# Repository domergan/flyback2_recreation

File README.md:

# Recreation of a Resonant Flyback Driver

A recreation of the Easy-Flyback driver by Franzoli Electronics: a resonant driver for CRT TV flyback transformers that produces high-voltage arcs, which can be audio-modulated to play music.
This repository contains a redrawn schematic and PCB layout based on his schematic published publicly on his page (https://franzolielectronics.com/easy-flyback-i/).

> All credit for the original circuit design goes to Franzoli!

&nbsp;

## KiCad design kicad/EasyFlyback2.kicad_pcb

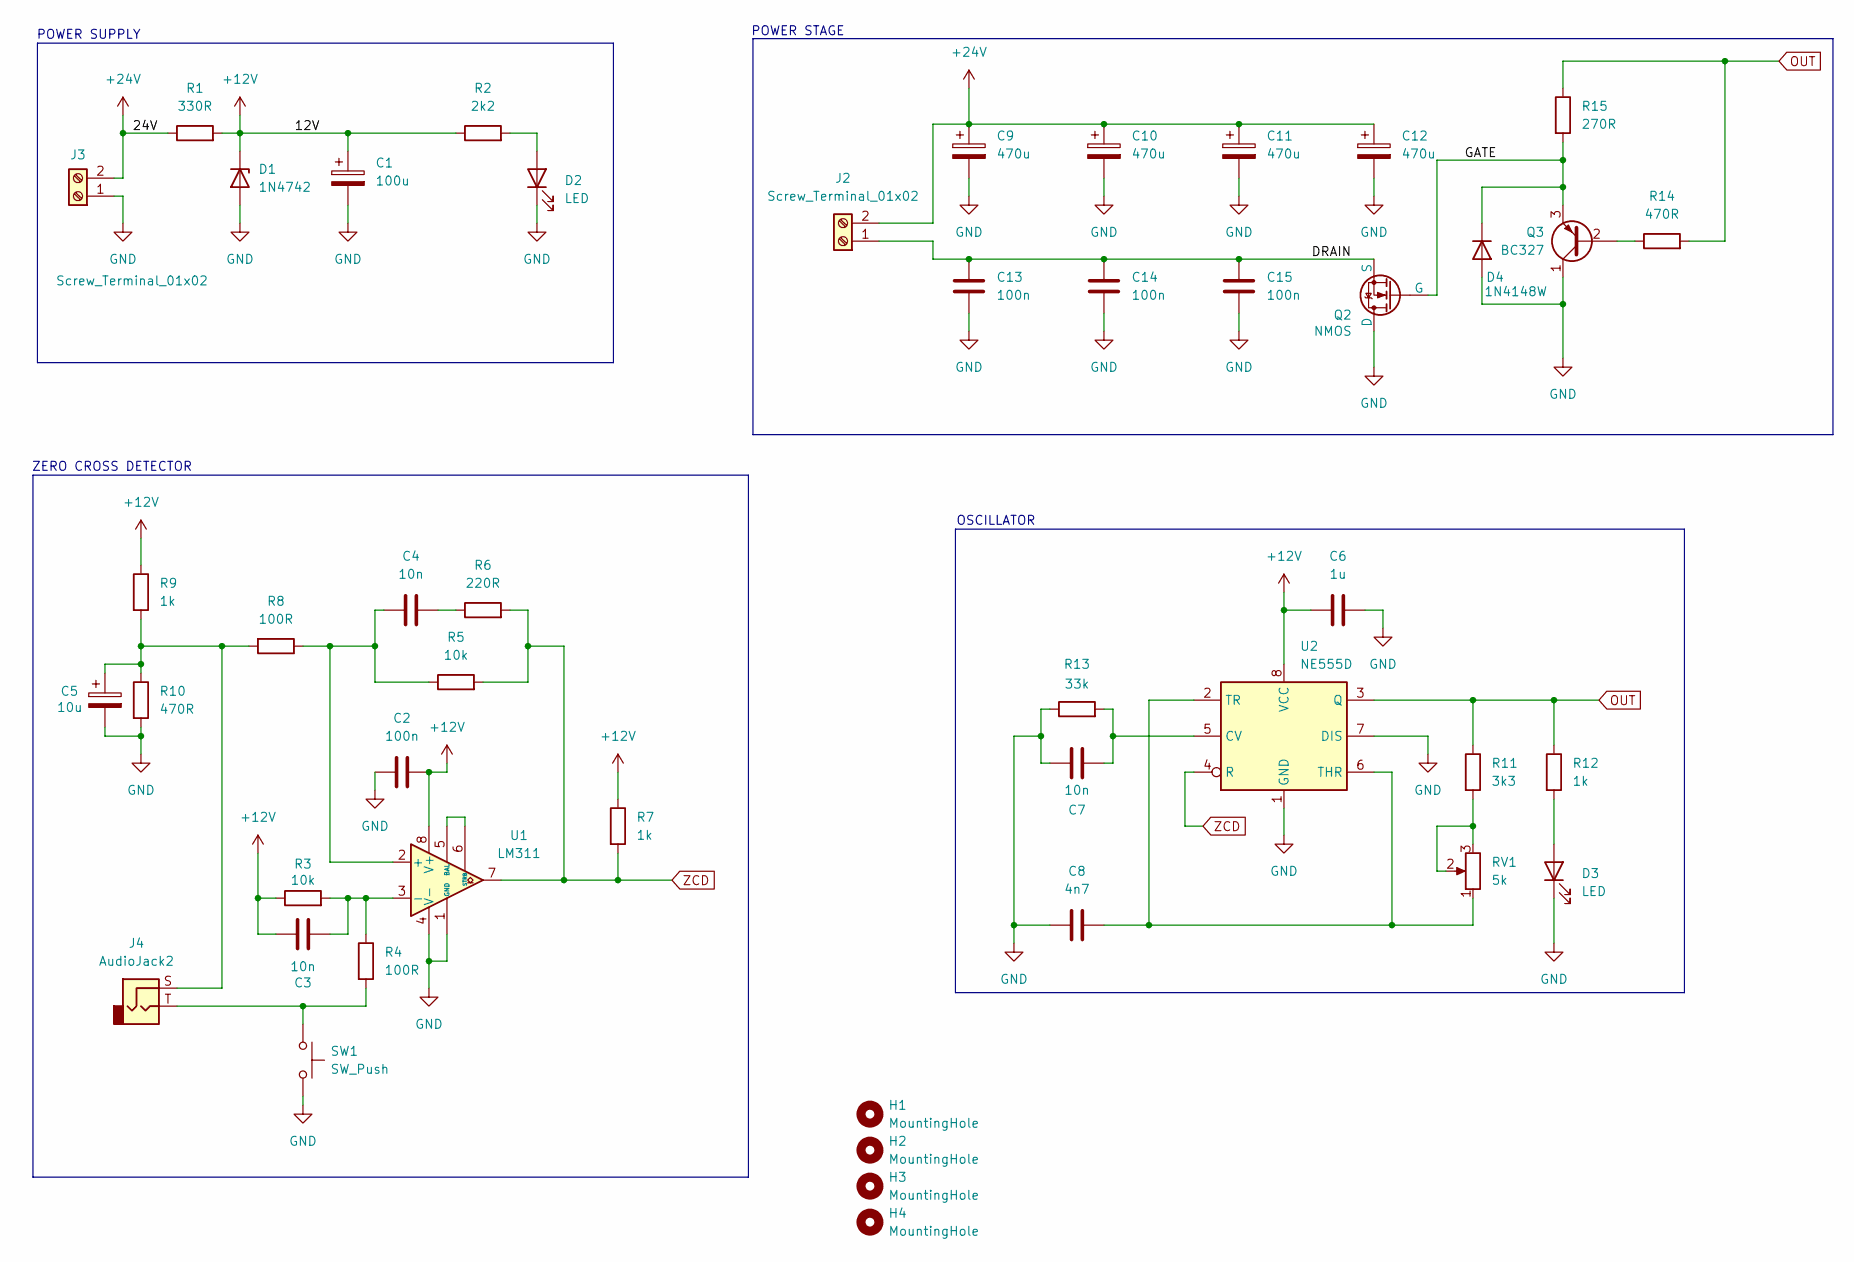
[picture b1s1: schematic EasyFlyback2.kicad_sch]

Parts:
C1: 100u; CP_Radial_D5.0mm_P2.00mm
C2: 100n; C_Rect_L7.0mm_W2.5mm_P5.00mm
C3, C4, C7: 10n; C_Rect_L7.0mm_W2.5mm_P5.00mm
C5: 10u; CP_Radial_D4.0mm_P1.50mm
C6: 1u; CP_Radial_D5.0mm_P2.00mm
C8: 4n7; C_Rect_L7.0mm_W2.5mm_P5.00mm
C9, C10, C11, C12: 470u; CP_Radial_D10.0mm_P5.00mm
C13, C14, C15: 100n; C_Rect_L18.0mm_W6.0mm_P15.00mm_FKS3_FKP3
D1: 1N4742; D_DO-41_SOD81_P7.62mm_Horizontal
D2, D3: LED; LED_D5.0mm
D4: 1N4148W; D_SOD-123
H1, H2, H3, H4: MountingHole; MountingHole_3.2mm_M3_ISO7380_Pad_TopOnly
J2, J3: Screw_Terminal_01x02; Altech_AK100_1x02_P5.00mm
J4: AudioJack2; Jack_3.5mm_CUI_SJ1-3525N_Horizontal
Q2: NMOS; TO-247-3_Horizontal_TabDown
Q3: BC327; TO-92_Inline
R1: 330R; R_Axial_DIN0516_L15.5mm_D5.0mm_P20.32mm_Horizontal
R2: 2k2; R_Axial_DIN0207_L6.3mm_D2.5mm_P10.16mm_Horizontal
R3, R5: 10k; R_Axial_DIN0207_L6.3mm_D2.5mm_P10.16mm_Horizontal
R4, R8: 100R; R_Axial_DIN0207_L6.3mm_D2.5mm_P10.16mm_Horizontal
R6: 220R; R_Axial_DIN0207_L6.3mm_D2.5mm_P10.16mm_Horizontal
R7, R9, R12: 1k; R_Axial_DIN0207_L6.3mm_D2.5mm_P10.16mm_Horizontal
R10, R14: 470R; R_Axial_DIN0207_L6.3mm_D2.5mm_P10.16mm_Horizontal
R11: 3k3; R_Axial_DIN0207_L6.3mm_D2.5mm_P10.16mm_Horizontal
R13: 33k; R_Axial_DIN0207_L6.3mm_D2.5mm_P10.16mm_Horizontal
R15: 270R; R_Axial_DIN0207_L6.3mm_D2.5mm_P10.16mm_Horizontal
RV1: 5k; Potentiometer_Bourns_3296W_Vertical
SW1: SW_Push; SW_PUSH_6mm
U1: LM311; DIP-8_W7.62mm_Socket
U2: NE555D; DIP-8_W7.62mm_Socket

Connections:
+12V: C1.1, C2.2, C3.1, C6.1, D1.1 (K), R1.2, R2.1, R3.1, R7.1, R9.1, U1.8 (V+), U2.8 (VCC)
+24V: C9.1, C10.1, C11.1, C12.1, J2.2, J3.2, R1.1
/DRAIN: C13.1, C14.1, C15.1, J2.1, Q2.3 (S)
/GATE: D4.1 (K), Q2.2 (G), Q3.3 (E), R15.2
GND: C1.2, C2.1, C5.2, C6.2, C7.1, C8.1, C9.2, C10.2, C11.2, C12.2, C13.2, C14.2, C15.2, D1.2 (A), D2.1 (K), D3.1 (K), D4.2 (A), J3.1, Q2.1 (D), Q3.1 (C), R10.2, R13.1, SW1.2, U1.1 (GND), U1.4 (V-), U2.1 (GND), U2.7 (DIS)
unnamed: C4.2, R6.1
unnamed: C5.1, J4.S, R8.2, R9.2, R10.1
unnamed: D2.2 (A), R2.2
unnamed: D3.2 (A), R12.2
unnamed: J4.T, R4.2, SW1.1
unnamed: Q3.2 (B), R14.1
unnamed: R11.2, RV1.2, RV1.3
unnamed: C4.1, R5.1, R8.1, U1.2 (+)
unnamed: C3.2, R3.2, R4.1, U1.3 (-)
unnamed: U1.5 (BAL), U1.6 (STRB)
unnamed: C7.2, R13.2, U2.5 (CV)
unnamed: C8.2, RV1.1, U2.2 (TR), U2.6 (THR)
OUT: R11.1, R12.1, R14.2, R15.1, U2.3 (Q)
ZCD: R5.2, R6.2, R7.2, U1.7, U2.4 (R)

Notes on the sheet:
OSCILLATOR
POWER SUPPLY
ZERO CROSS DETECTOR
POWER STAGE

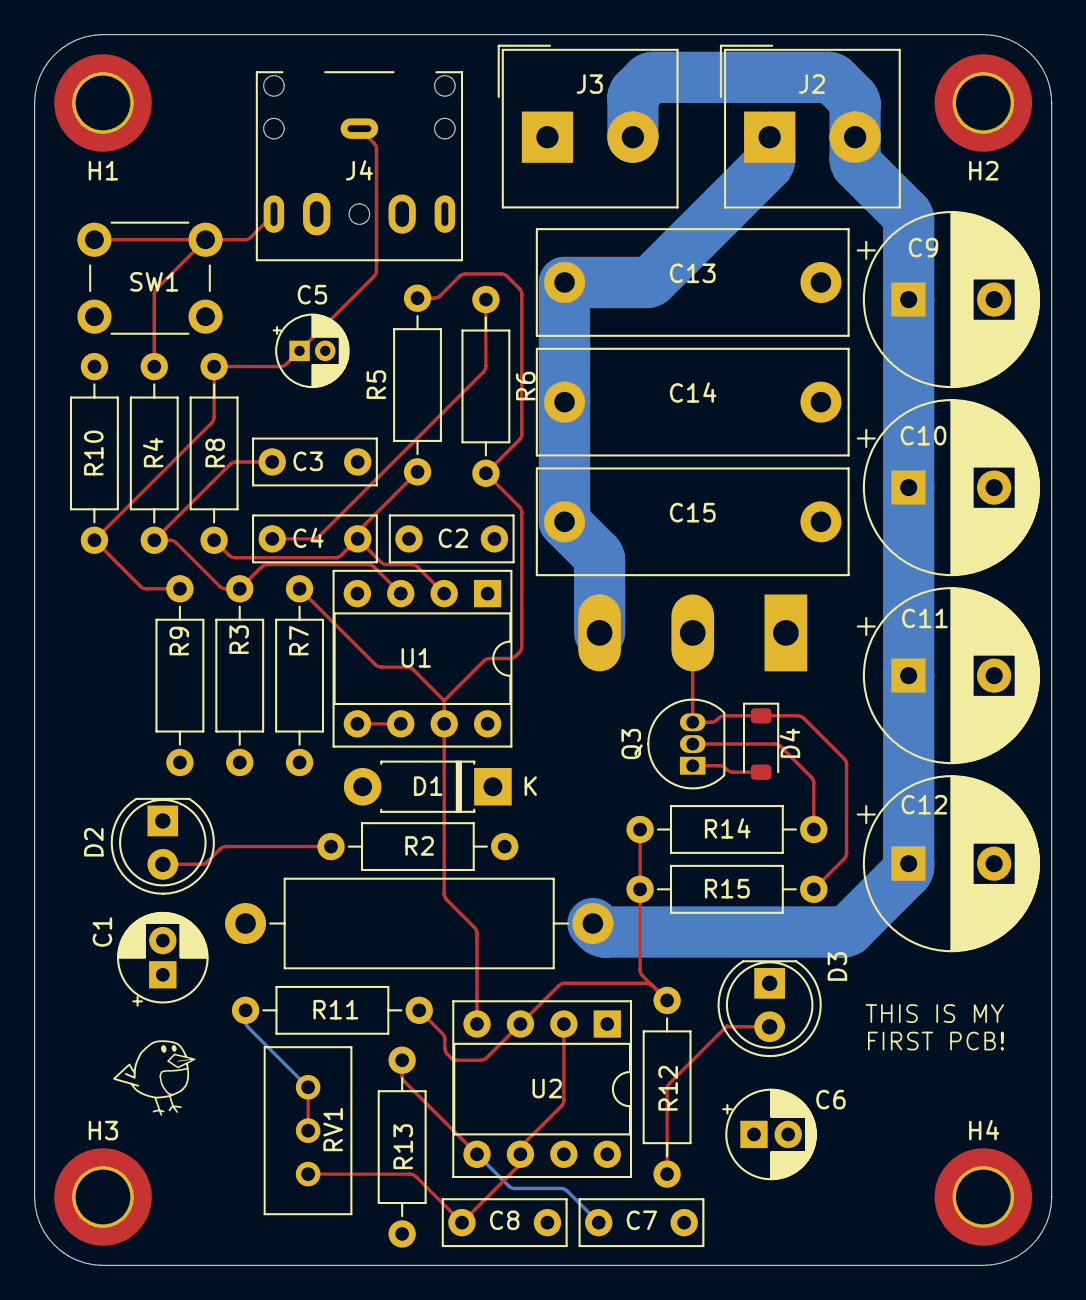
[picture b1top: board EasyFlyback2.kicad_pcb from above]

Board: 4 copper layers, 59.5 x 72.0 mm, 47 parts (0 on the bottom side), 19 nets.
